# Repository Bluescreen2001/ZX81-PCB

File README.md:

# ZX81-PCB

Recreation of the original ZX81 Issue1 PCB with rounded traces, and the WespiNano, a tiny version of the Wespi.

## DISCLAIMER:

This is for personal use only. You may not sell this design without contacting me.

## Description:

The Sinclair ZX81 was one of the first home computers. There are several PCB versions out there, but the film for the first version was created 
manually with clear foil and stickers and pen. This first version (Issue One) is rare but it is "the original" with non CAD like rounded traces.

One day some people from the German Sinclair [ZX81 forum](https://forum.tlienhard.com) diskussed how this PCB can be recreated.
So I took a photo from front and back side of the PCB with a scanner, put this as a background images in my CAD application and redraw all the traces. 
The resulting DXF file was then imported into EAGLE and than mapped to an EAGLE schematic, so I get a consistent EAGLE project. After some fine tuning 
I got a PCB design which was nearly like the original.

After some diskussions we decided to create a slightly altered version with some "modern" features. See the following chapter ...

## Versions:

### Issue 1:

This is the most authentic version. Nearly like the original with nothing changed at all:

- modulator
- old EPROM
- single resistors instead of SIL arrays

### Issue 1a:

Like Issue 1 above, but a slightly improved silkscreen. Some single resistors are replaced with SIL arrays, but no changes to the PCB traces, 
besides some cosmetic corrections

### Issue 1b:

Some functional addons:

- added connector for a small VideoOut board "under" the modulator footprint. You can omit the modulator and place this connector to add the 
  videoOut board to get an video out connector instead of the RF output. You can also add a WespNano (see below) to get WiFi, Storage and VGA.
- added footprint for a "modern" EPROM with two jumpers to select the page you like.
- added "Fast Wait" logic with a disable jumper
- added a jumper for vLA81 support. This routes the OSC pin of the ULA to A13 of the RAM, so you can use ...
- modern CMOS RAM up to 32 kB, supported by the vLA81

### Issue 1c:

- added an reset button
- added a second mounting hole for the VideoOut board for better stability.

## Addons

### VideoOut

A small addon board fitting onto Issue 1b and higher that features a buffered composite video out cinch connector

### Wespi-Nano

This is a tiny version of the Wespi project from the [ZX81 forum](https://forum.tlienhard.com). It uses an esp32 to scan the video signal to create 
a VGA or TFT video signal. Also it can send files to the ZX's tape input using a fastload mechanism. The files came from the esp's onboard flash memory 
which can be populated using a web interface from your PC or mobile. Loading is initiated by an onscreen menu on the ZX81 screen via load command.

## Hints:
In every subdirectory you find a *_Gerbers.zip. This are the files you need to create the PCB by any PCB manufacturer like JLCPCB.
In the doc directory are some photos and a nice German manual.

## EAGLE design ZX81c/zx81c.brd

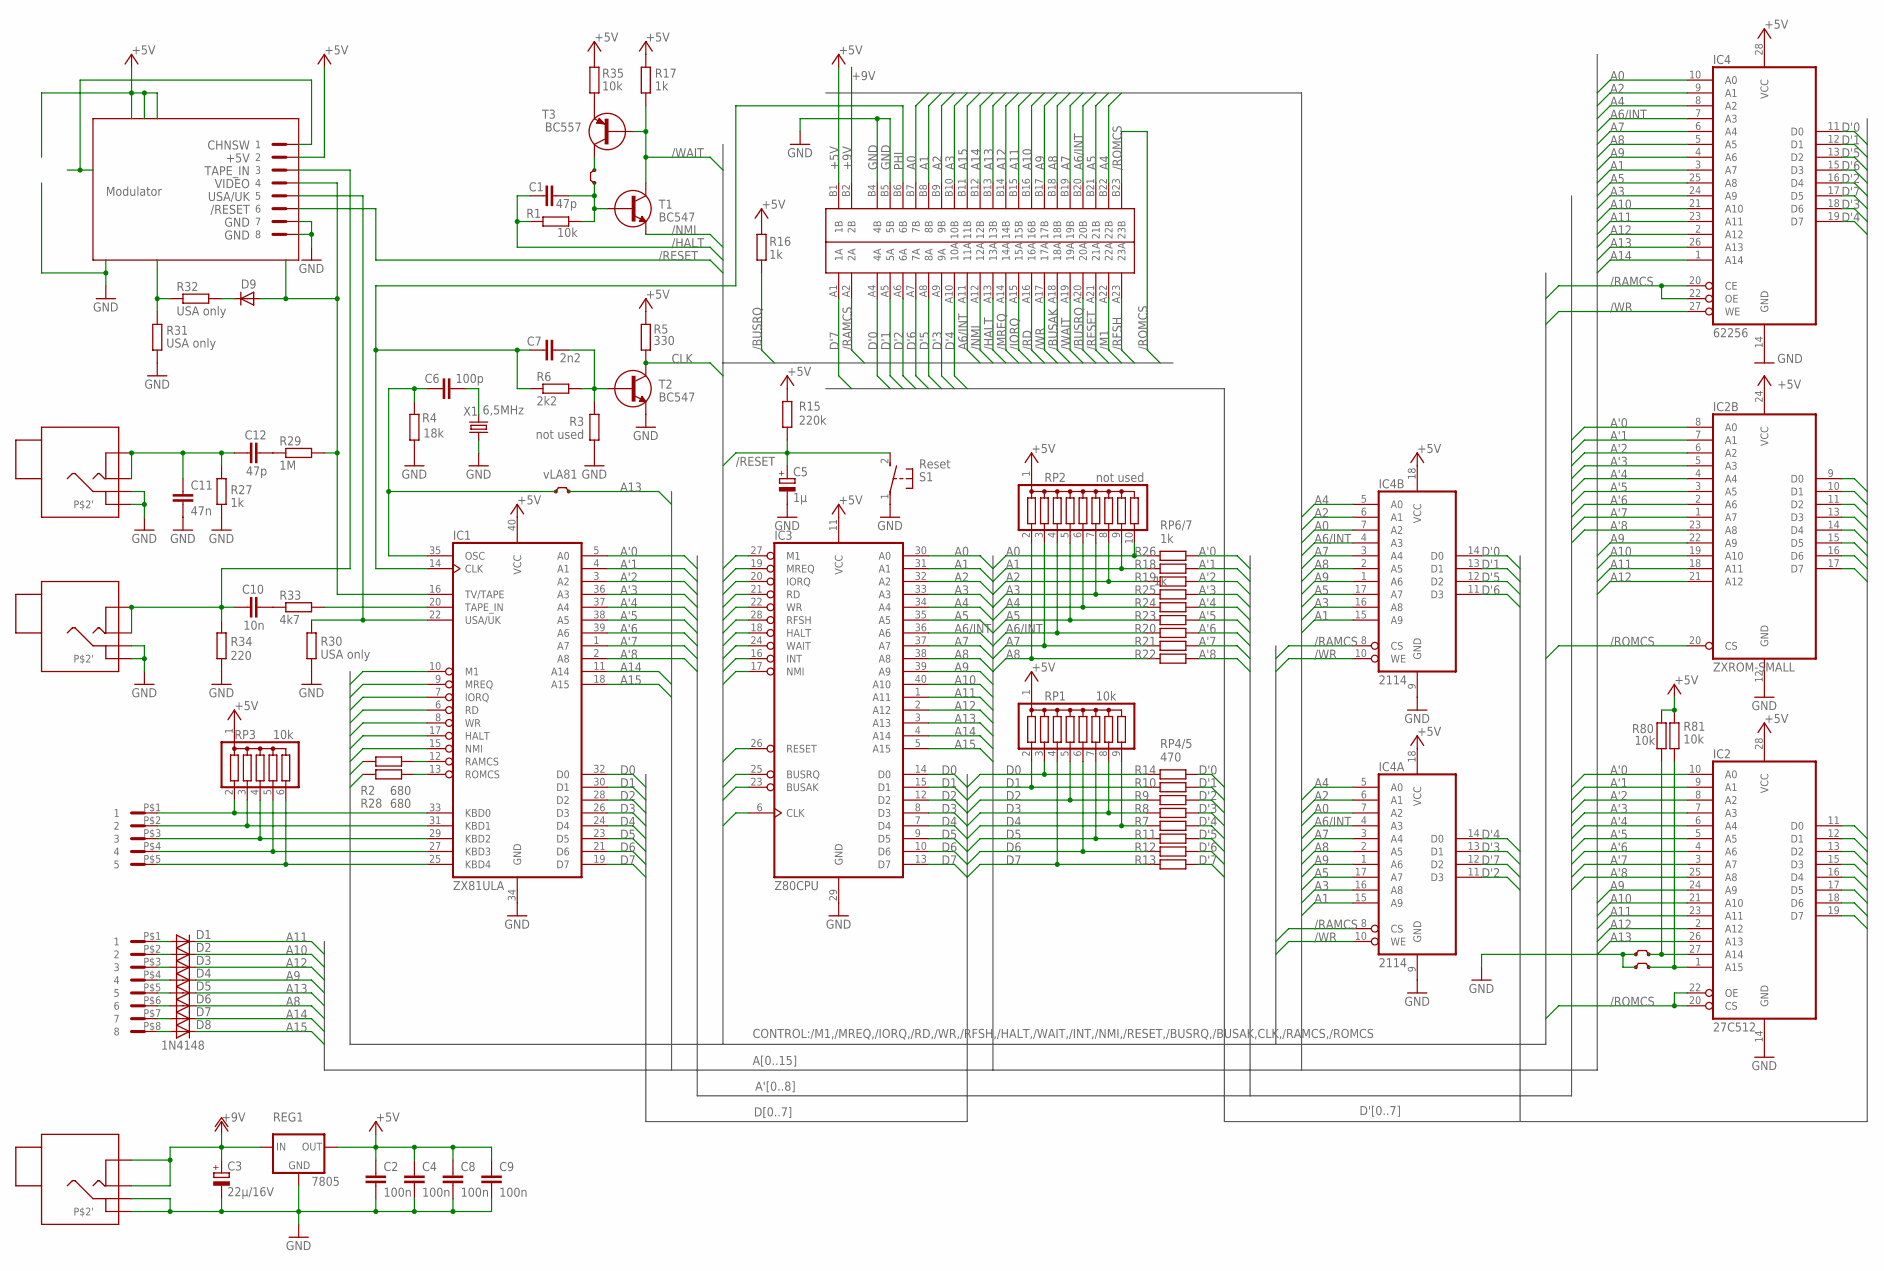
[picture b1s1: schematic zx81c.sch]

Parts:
C1, C12: 47p; C025-025X050
C2, C4, C8, C9: 100n; C025-025X050
C3: 22µ/16V; E5-5
C5: 1µ; E3,8-5
C6: 100p; C025-025X050
C7: 2n2; C025-025X050
C10: 10n; C025-025X050
C11: 47n; C025-025X050
D1, D2, D3, D4, D5, D6, D7, D8: 1N4148; D-TR-10
D9: DIODED15; D15
IC1: ZX81ULA; DIL40
IC2: 27C512; DIL28
IC2B: ZXROM-SMALL; DIL24
IC3: Z80CPU; DIL40
IC4: 62256; DIL28
IC4A, IC4B: 2114; DIL18
JP1, JP2, JP3, JP4: JUMPER
K1: ZX81CONN; ZX81CON
K2: MIC; ZXKLINKE4POL
K3: EAR; ZXKLINKE4POL
K4: DCIN; ZXKLINKE4POL
K5: PINHEAD-2X4; PINHEAD2X4
KB1: ZXKBD5CON; ZXKDB5
KB2: ZXKBD8CON; ZXKBD8
R1, R35, R80, R81: 10k; R207/12
R2, R28: 680; R207/12
R3: not used; R207/12
R4: 18k; R207/12
R5: 330; R207/12
R6: 2k2; R207/12
R15: 220k; R207/12
R16, R17, R27: 1k; R207/12
R29: 1M; R207/12
R30, R31, R32: USA only; R207/12
R33: 4k7; R207/12
R34: 220; R207/12
REG1: 7805; 78XXL
RP1: 10k; SIL9
RP2: not used; SIL10
RP3: 10k; SIL6
RP4, RP5: 470; SIL8P
RP6: 1k; SIL8P
RP7: 1k; SIL10P
S1: Reset; B3F-31XX
T1, T2: BC547; TO92
T3: BC557; TO92
X1: 6,5MHz; HC49

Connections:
+5V: C2.1, C4.1, C8.1, C9.1, IC1.40 (VCC), IC2.28 (VCC), IC2B.24 (VCC), IC3.11 (VCC), IC4.28 (VCC), IC4A.18 (VCC), IC4B.18 (VCC), K1.B1 (1B), K5.2, R5.2, R15.2, R16.1, R17.2, R35.2, R80.2, R81.2, REG1.OUT, RP1.1, RP2.1, RP3.1
+9V: C3.+, K1.B2 (2B), K4.1, K4.1', REG1.IN
/BUSAK: IC3.23 (BUSAK), K1.A18 (18A)
/BUSRQ: IC3.25 (BUSRQ), K1.A20 (20A), R16.2
/HALT: C1.1, IC1.17 (HALT), IC3.18 (HALT), K1.A13 (13A), R1.1
/IORQ: IC1.7 (IORQ), IC3.20 (IORQ), K1.A15 (15A)
/M1: IC1.10 (M1), IC3.27 (M1), K1.A22 (22A)
/MREQ: IC1.9 (MREQ), IC3.19 (MREQ), K1.A14 (14A)
/NMI: IC1.15 (NMI), IC3.17 (NMI), K1.A12 (12A), T1.E
/RAMCS: IC4.20 (CE), IC4.22 (OE), IC4A.8 (CS), IC4B.8 (CS), K1.A2 (2A), R2.2
/RD: IC1.6 (RD), IC3.21 (RD), K1.A16 (16A)
/RESET: C5.+, IC3.26 (RESET), K1.A21 (21A), K5.6, R15.1, S1.2 (S)
/RFSH: IC3.28 (RFSH), K1.A23 (23A)
/ROMCS: IC2.20 (CS), IC2.22 (OE), IC2B.20 (CS), K1.B23 (23B), R28.2
/WAIT: IC3.24 (WAIT), K1.A19 (19A), R17.1, T1.C, T3.B
/WR: IC1.8 (WR), IC3.22 (WR), IC4.27 (WE), IC4A.10 (WE), IC4B.10 (WE), K1.A17 (17A)
A0: IC3.30 (A0), IC4.10 (A0), IC4A.7 (A2), IC4B.7 (A2), K1.B7 (7B), RP2.10, RP6.8 (2)
A1: IC3.31 (A1), IC4.3 (A7), IC4A.15 (A9), IC4B.15 (A9), K1.B8 (8B), RP2.9, RP7.1
A2: IC3.32 (A2), IC4.9 (A1), IC4A.6 (A1), IC4B.6 (A1), K1.B9 (9B), RP2.8, RP7.4 (2)
A3: IC3.33 (A3), IC4.24 (A9), IC4A.16 (A8), IC4B.16 (A8), K1.B10 (10B), RP2.7, RP6.6 (2)
A4: IC3.34 (A4), IC4.8 (A2), IC4A.5 (A0), IC4B.5 (A0), K1.B22 (22B), RP2.6, RP6.4 (2)
A5: IC3.35 (A5), IC4.25 (A8), IC4A.17 (A7), IC4B.17 (A7), K1.B21 (21B), RP2.5, RP6.2
A6/INT: IC3.16 (INT), IC3.36 (A6), IC4.7 (A3), IC4A.4 (A3), IC4B.4 (A3), K1.A11 (11A), K1.B20 (20B), RP2.4, RP7.6 (2)
A7: IC3.37 (A7), IC4.6 (A4), IC4A.3 (A4), IC4B.3 (A4), K1.B19 (19B), RP2.3, RP7.8 (2)
A8: D6.C, IC3.38 (A8), IC4.5 (A5), IC4A.2 (A5), IC4B.2 (A5), K1.B18 (18B), RP2.2, RP7.10 (2)
A9: D4.C, IC2.24 (A9), IC2B.22 (A9), IC3.39 (A9), IC4.4 (A6), IC4A.1 (A6), IC4B.1 (A6), K1.B17 (17B)
A10: D2.C, IC2.21 (A10), IC2B.19 (A10), IC3.40 (A10), IC4.21 (A10), K1.B16 (16B)
A11: D1.C, IC2.23 (A11), IC2B.18 (A11), IC3.1 (A11), IC4.23 (A11), K1.B15 (15B)
A12: D3.C, IC2.2 (A12), IC2B.21 (A12), IC3.2 (A12), IC4.2 (A12), K1.B14 (14B)
A13: D5.C, IC2.26 (A13), IC3.3 (A13), IC4.26 (A13), JP3.2, K1.B13 (13B)
A14: D7.C, IC1.11 (A14), IC3.4 (A14), IC4.1 (A14), K1.B12 (12B)
A15: D8.C, IC1.18 (A15), IC3.5 (A15), K1.B11 (11B)
A'0: IC1.5 (A0), IC2.10 (A0), IC2B.8 (A0), RP6.7 (1)
A'1: IC1.4 (A1), IC2.9 (A1), IC2B.7 (A1), RP7.2
A'2: IC1.3 (A2), IC2.8 (A2), IC2B.6 (A2), RP7.3 (1)
A'3: IC1.36 (A3), IC2.7 (A3), IC2B.5 (A3), RP6.5 (1)
A'4: IC1.37 (A4), IC2.6 (A4), IC2B.4 (A4), RP6.3 (1)
A'5: IC1.38 (A5), IC2.5 (A5), IC2B.3 (A5), RP6.1
A'6: IC1.39 (A6), IC2.4 (A6), IC2B.2 (A6), RP7.5 (1)
A'7: IC1.1 (A7), IC2.3 (A7), IC2B.1 (A7), RP7.7 (1)
A'8: IC1.2 (A8), IC2.25 (A8), IC2B.23 (A8), RP7.9 (1)
CHNSW: K5.1
CLK: IC3.6 (CLK), R5.1, T2.C
D0: IC1.32 (D0), IC3.14 (D0), RP1.3, RP5.7 (1)
D1: IC1.30 (D1), IC3.15 (D1), RP1.2, RP4.7 (1)
D2: IC1.28 (D2), IC3.12 (D2), RP1.5, RP4.5 (1)
D3: IC1.26 (D3), IC3.8 (D3), RP1.8, RP4.3 (1)
D4: IC1.24 (D4), IC3.7 (D4), RP1.9, RP4.2
D5: IC1.23 (D5), IC3.9 (D5), RP1.7, RP5.2
D6: IC1.21 (D6), IC3.10 (D6), RP1.6, RP5.3 (1)
D7: IC1.19 (D7), IC3.13 (D7), RP1.4, RP5.6 (2)
D'0: IC2.11 (D0), IC2B.9 (D0), IC4.11 (D0), IC4B.14 (D0), K1.A4 (4A), RP5.8 (2)
D'1: IC2.12 (D1), IC2B.10 (D1), IC4.12 (D1), IC4B.13 (D1), K1.A5 (5A), RP4.8 (2)
D'2: IC2.13 (D2), IC2B.11 (D2), IC4.16 (D4), IC4A.11 (D3), K1.A6 (6A), RP4.6 (2)
D'3: IC2.15 (D3), IC2B.13 (D3), IC4.18 (D6), IC4A.13 (D1), K1.A9 (9A), RP4.4 (2)
D'4: IC2.16 (D4), IC2B.14 (D4), IC4.19 (D7), IC4A.14 (D0), K1.A10 (10A), RP4.1
D'5: IC2.17 (D5), IC2B.15 (D5), IC4.13 (D2), IC4B.12 (D2), K1.A8 (8A), RP5.1
D'6: IC2.18 (D6), IC2B.16 (D6), IC4.15 (D3), IC4B.11 (D3), K1.A7 (7A), RP5.4 (2)
D'7: IC2.19 (D7), IC2B.17 (D7), IC4.17 (D5), IC4A.12 (D2), K1.A1 (1A), RP5.5 (1)
GND: C2.2, C3.-, C4.2, C5.-, C8.2, C9.2, C11.2, IC1.34 (GND), IC2.14 (GND), IC2B.12 (GND), IC3.29 (GND), IC4.14 (GND), IC4A.9 (GND), IC4B.9 (GND), JP1.1, JP2.1, K1.B4 (4B), K1.B5 (5B), K2.2, K2.2', K3.2, K3.2', K4.2, K4.2', K5.7, K5.8, R3.1, R4.1, R27.1, R30.2, R31.1, R34.1, REG1.GND, S1.1, T2.E, X1.1
KBD0: IC1.33 (KBD0), KB1.P$1 (1), RP3.2
KBD1: IC1.31 (KBD1), KB1.P$2 (2), RP3.3
KBD2: IC1.29 (KBD2), KB1.P$3 (3), RP3.4
KBD3: IC1.27 (KBD3), KB1.P$4 (4), RP3.5
KBD4: IC1.25 (KBD4), KB1.P$5 (5), RP3.6
unnamed: IC1.12 (RAMCS), R2.1
unnamed: IC1.13 (ROMCS), R28.1
unnamed: C1.2, JP4.1, R1.2, T1.B
unnamed: C6.2, X1.2
unnamed: C6.1, IC1.35 (OSC), JP3.1, R4.2
unnamed: C7.2, R3.2, R6.2, T2.B
unnamed: IC2.27 (A14), JP1.2, R80.1
unnamed: D1.A, KB2.P$1 (1)
unnamed: D2.A, KB2.P$2 (2)
unnamed: D3.A, KB2.P$3 (3)
unnamed: D4.A, KB2.P$4 (4)
unnamed: D5.A, KB2.P$5 (5)
unnamed: D6.A, KB2.P$6 (6)
unnamed: D7.A, KB2.P$7 (7)
unnamed: D8.A, KB2.P$8 (8)
unnamed: C10.2, R33.1
unnamed: C12.2, R29.1
unnamed: IC2.1 (A15), JP2.2, R81.1
unnamed: D9.C, R32.2
unnamed: R35.1, T3.E
unnamed: R31.2, R32.1
unnamed: JP4.2, T3.C
PHI: C7.1, IC1.14 (CLK), K1.B6 (6B), R6.1
TAPEIN: IC1.20 (TAPE_IN), R33.2
TAPE_IN: C10.1, K3.1, K3.1', K5.3, R34.2
TAPE_OUT: C11.1, C12.1, K2.1, K2.1', R27.2
USA/UK: IC1.22 (USA/UK), K5.5, R30.1
VIDEO: D9.A, IC1.16 (TV/TAPE), K5.4, R29.2

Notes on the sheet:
R10
R12
R13
R11
R14
RP4/5 470
R26
R18
R19
R25
R24
R23
R20
R21
R22
RP6/7 1k
Modulator
vLA81

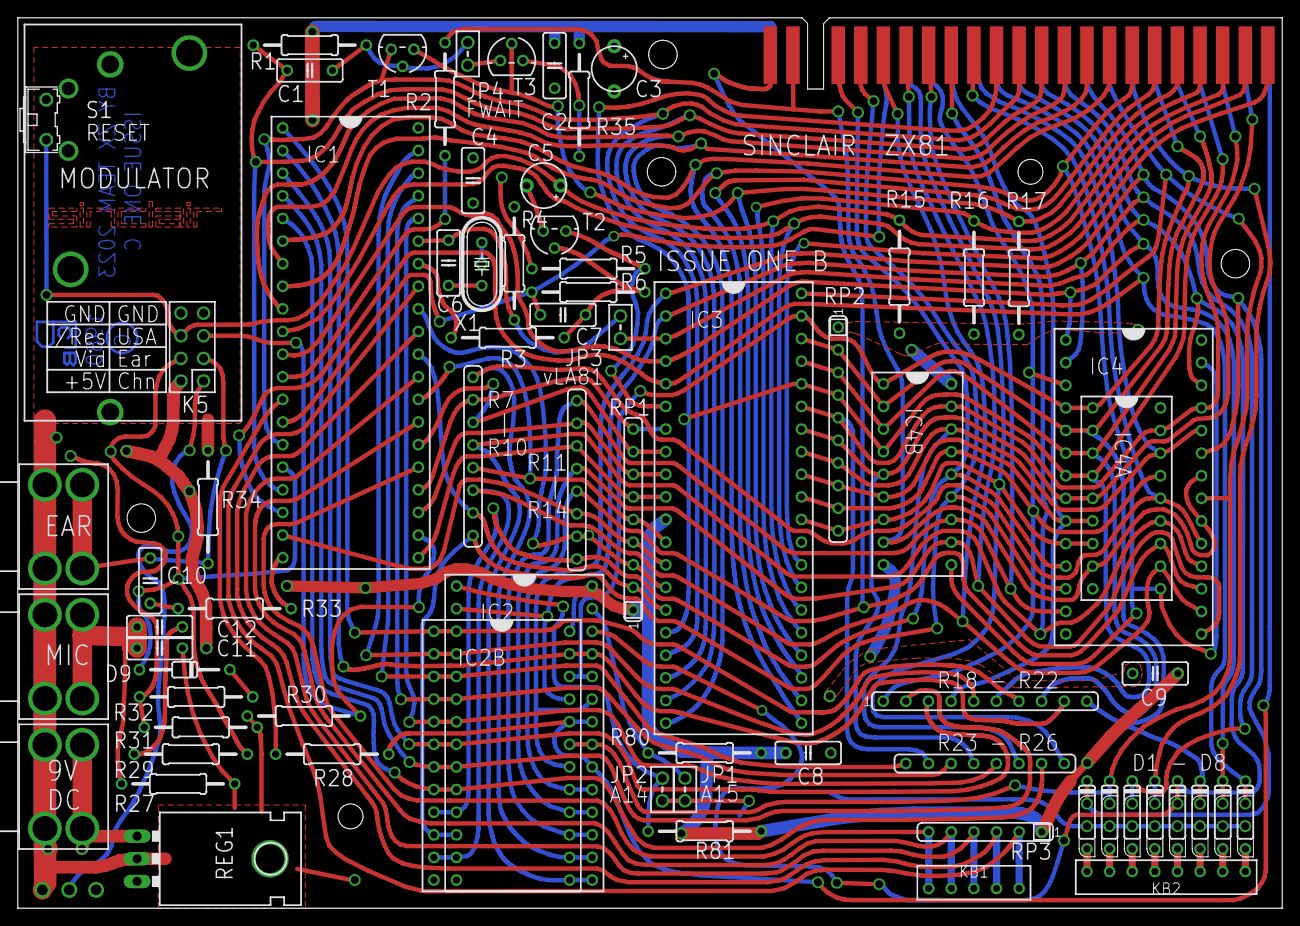
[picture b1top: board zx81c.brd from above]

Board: 2 copper layers, 142.0 x 100.0 mm, 72 parts (0 on the bottom side), 92 nets.

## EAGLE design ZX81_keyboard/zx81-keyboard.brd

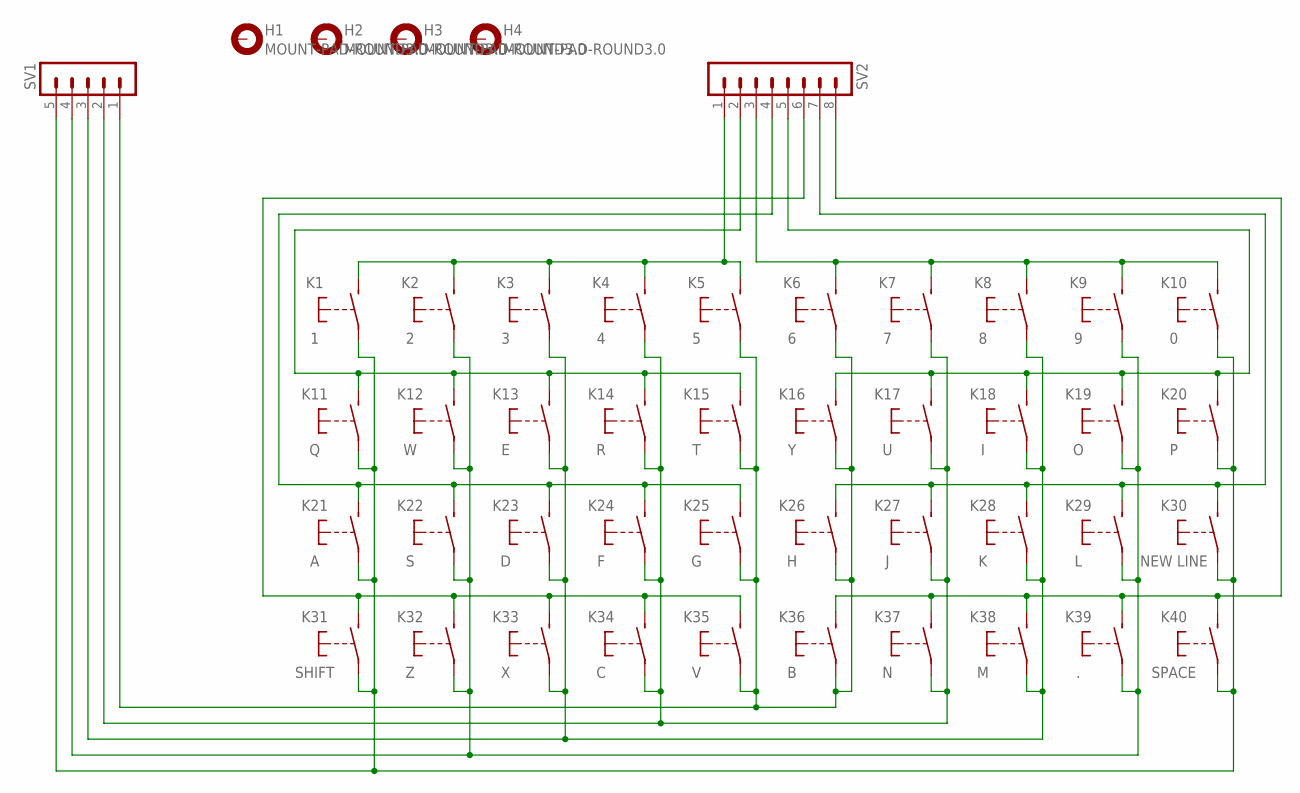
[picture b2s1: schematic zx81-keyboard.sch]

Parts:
H1, H2, H3, H4: MOUNT-PAD-ROUND3.0; 3,0-PAD
K1: 1; MARQUARTDT-6425
K2: 2; MARQUARTDT-6425
K3: 3; MARQUARTDT-6425
K4: 4; MARQUARTDT-6425
K5: 5; MARQUARTDT-6425
K6: 6; MARQUARTDT-6425
K7: 7; MARQUARTDT-6425
K8: 8; MARQUARTDT-6425
K9: 9; MARQUARTDT-6425
K10: 0; MARQUARTDT-6425
K11: Q; MARQUARTDT-6425
K12: W; MARQUARTDT-6425
K13: E; MARQUARTDT-6425
K14: R; MARQUARTDT-6425
K15: T; MARQUARTDT-6425
K16: Y; MARQUARTDT-6425
K17: U; MARQUARTDT-6425
K18: I; MARQUARTDT-6425
K19: O; MARQUARTDT-6425
K20: P; MARQUARTDT-6425
K21: A; MARQUARTDT-6425
K22: S; MARQUARTDT-6425
K23: D; MARQUARTDT-6425
K24: F; MARQUARTDT-6425
K25: G; MARQUARTDT-6425
K26: H; MARQUARTDT-6425
K27: J; MARQUARTDT-6425
K28: K; MARQUARTDT-6425
K29: L; MARQUARTDT-6425
K30: NEW LINE; MARQUARTDT-6425
K31: SHIFT; MARQUARTDT-6425
K32: Z; MARQUARTDT-6425
K33: X; MARQUARTDT-6425
K34: C; MARQUARTDT-6425
K35: V; MARQUARTDT-6425
K36: B; MARQUARTDT-6425
K37: N; MARQUARTDT-6425
K38: M; MARQUARTDT-6425
K39: .; MARQUARTDT-6425
K40: SPACE; MARQUARTDT-6425
SV1: MA05-1
SV2: MA08-1

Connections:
unnamed: K1.P$2 (S), K2.P$2 (S), K3.P$2 (S), K4.P$2 (S), K5.P$2 (S), SV2.1
unnamed: K6.P$2 (S), K7.P$2 (S), K8.P$2 (S), K9.P$2 (S), K10.P$2 (S), SV2.3
unnamed: K11.P$2 (S), K12.P$2 (S), K13.P$2 (S), K14.P$2 (S), K15.P$2 (S), SV2.2
unnamed: K21.P$2 (S), K22.P$2 (S), K23.P$2 (S), K24.P$2 (S), K25.P$2 (S), SV2.4
unnamed: K31.P$2 (S), K32.P$2 (S), K33.P$2 (S), K34.P$2 (S), K35.P$2 (S), SV2.6
unnamed: K16.P$2 (S), K17.P$2 (S), K18.P$2 (S), K19.P$2 (S), K20.P$2 (S), SV2.5
unnamed: K26.P$2 (S), K27.P$2 (S), K28.P$2 (S), K29.P$2 (S), K30.P$2 (S), SV2.7
unnamed: K36.P$2 (S), K37.P$2 (S), K38.P$2 (S), K39.P$2 (S), K40.P$2 (S), SV2.8
unnamed: K5.P$1, K6.P$1, K15.P$1, K16.P$1, K25.P$1, K26.P$1, K35.P$1, K36.P$1, SV1.1
unnamed: K4.P$1, K7.P$1, K14.P$1, K17.P$1, K24.P$1, K27.P$1, K34.P$1, K37.P$1, SV1.2
unnamed: K3.P$1, K8.P$1, K13.P$1, K18.P$1, K23.P$1, K28.P$1, K33.P$1, K38.P$1, SV1.3
unnamed: K2.P$1, K9.P$1, K12.P$1, K19.P$1, K22.P$1, K29.P$1, K32.P$1, K39.P$1, SV1.4
unnamed: K1.P$1, K10.P$1, K11.P$1, K20.P$1, K21.P$1, K30.P$1, K31.P$1, K40.P$1, SV1.5

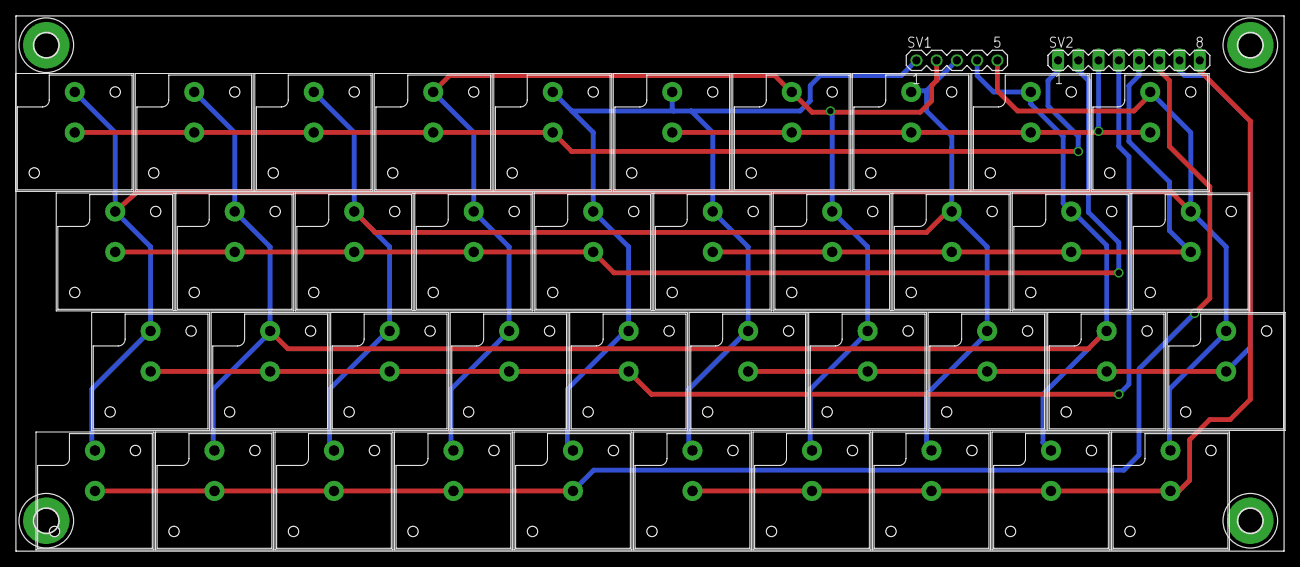
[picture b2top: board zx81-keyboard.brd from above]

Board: 2 copper layers, 159.2 x 67.2 mm, 46 parts (0 on the bottom side), 13 nets.

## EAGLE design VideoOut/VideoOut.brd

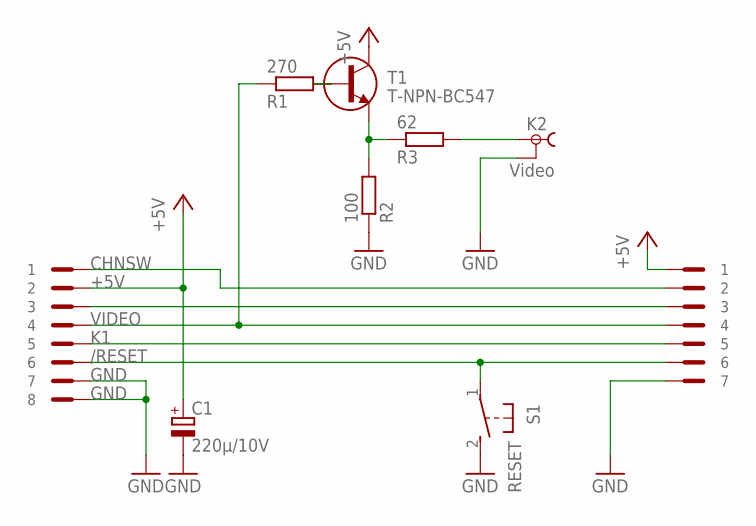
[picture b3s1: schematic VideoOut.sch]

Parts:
C1: 220µ/10V; E2,5-6
K2: Video; TOBU3
K3: PINHEAD-1X7; PINHEAD1X7
K6: PINHEAD-2X4; PINHEAD2X4
R1: 270; R207/10
R2: 100; R207/10
R3: 62; R207/10
S1: RESET; B3F-31XX
T1: T-NPN-BC547; TO92

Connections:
+5V: C1.+, K3.1, K6.2, T1.C
/RESET: K3.6, K6.6, S1.1
CHNSW: K3.2, K6.1
GND: C1.-, K2.2, K2.2@1 (2), K2.2@2 (2), K3.7, K6.7, K6.8, R2.1, S1.2 (S)
K1: K3.5, K6.5
unnamed: K3.3, K6.3
unnamed: R1.2, T1.B
unnamed: R2.2, R3.1, T1.E
unnamed: K2.1, R3.2
VIDEO: K3.4, K6.4, R1.1

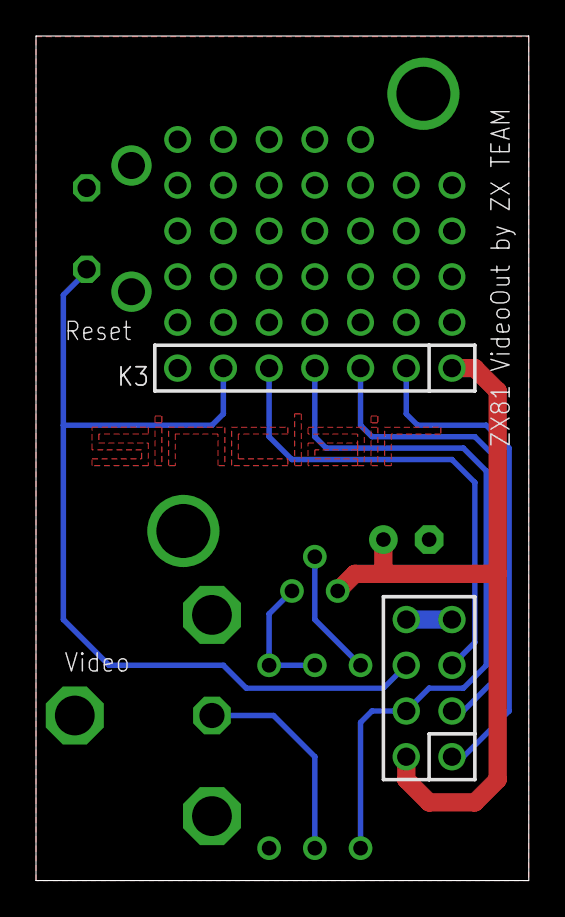
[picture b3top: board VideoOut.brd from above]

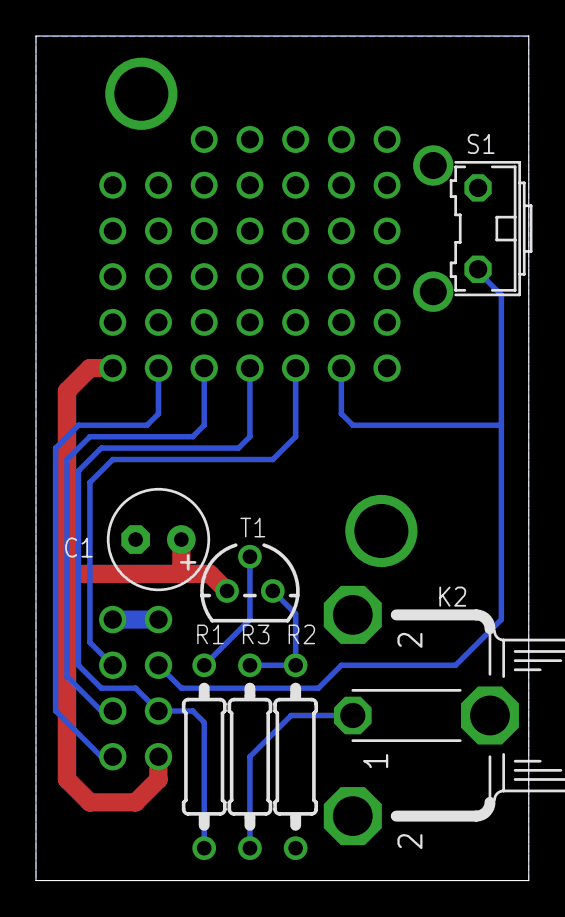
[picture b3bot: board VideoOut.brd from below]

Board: 2 copper layers, 27.4 x 46.9 mm, 9 parts (7 on the bottom side), 10 nets.

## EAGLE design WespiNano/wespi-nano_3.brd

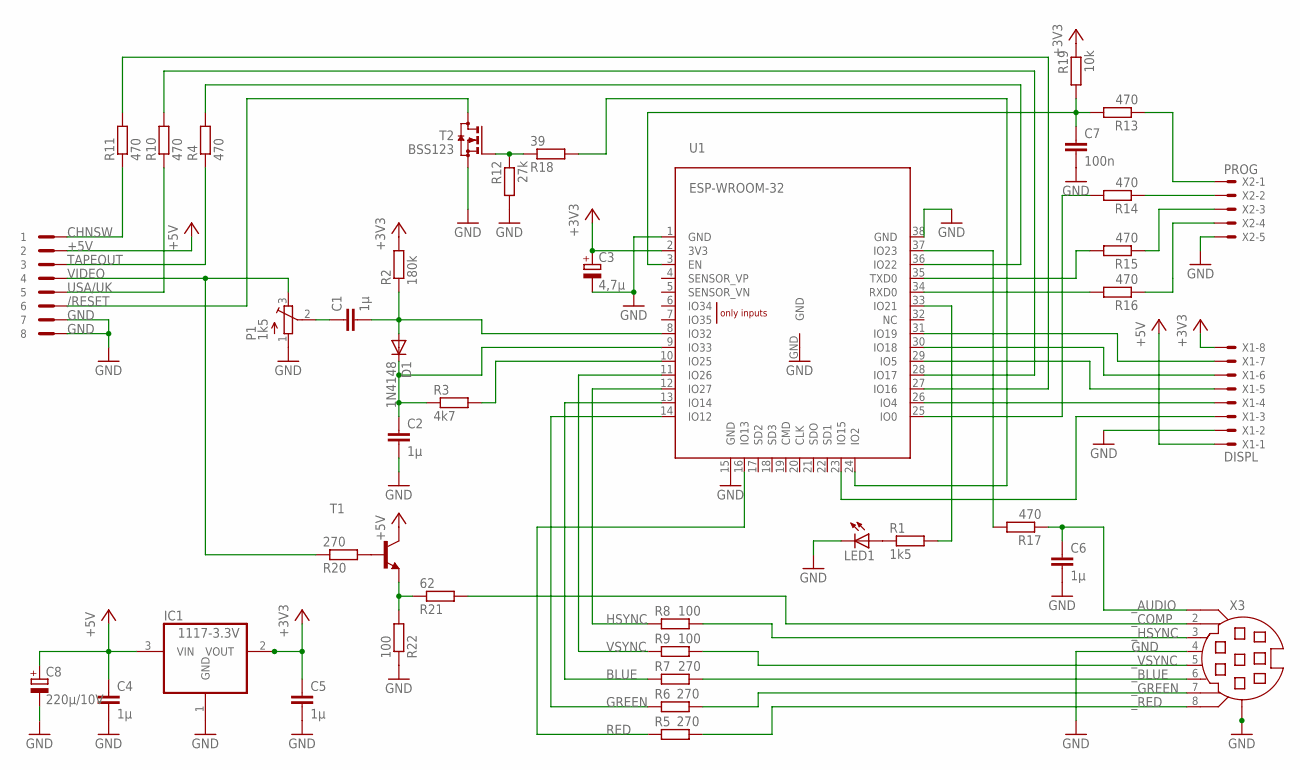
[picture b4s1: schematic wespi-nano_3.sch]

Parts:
C1, C2, C4, C5, C6: 1µ; C0805
C3: 4,7µ; 153CLV-0405
C7: 100n; C0805
C8: 220µ/10V; E2,5-6
D1: 1N4148; SOD-123_MINI-SMA
IC1: 1117-3.3V; SOT223
K6: PINHEAD-2X4; PINHEAD2X4
LED1: LEDSML0805; SML0805
P1: 1k5; 3223G
R1: 1k5; R0805
R2: 180k; R0805
R3: 4k7; R0805
R4, R10, R11, R13, R14, R15, R16, R17: 470; R0805
R5, R6, R7, R20: 270; R0805
R8, R9, R22: 100; R0805
R12: 27k; R0805
R18: 39; R0805
R19: 10k; R0805
R21: 62; R0805
T1: BC847-NPN-SOT23-BEC; SOT23-BEC
T2: BSS123; SOT23
U1: ESP-WROOM-32
X1: DISPL; 53047-08
X2: PROG; 53047-05
X3: MINI-DIN-8

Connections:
+3V3: C3.+, C5.1, IC1.2 (VOUT), IC1.4 (VOUT1), R2.2, R19.1, U1.2 (3V3), X1.8
+5V: C4.1, C8.+, IC1.3 (VIN), K6.2, T1.C, X1.1
/RESET: K6.6, T2.3 (D)
BLUE: R7.1, U1.13 (IO14)
BOOT0: R14.1, X2.2
CHNSW: K6.1, R11.1
GND: C2.2, C3.-, C4.2, C5.2, C6.2, C7.2, C8.-, IC1.1 (GND), K6.7, K6.8, LED1.C, P1.1 (A), R12.2, R22.1, T2.2 (S), U1.1 (GND), U1.15 (GND), U1.38 (GND), U1.GND, X1.2, X2.5, X3.4, X3.G (G1), X3.G1 (G2), X3.G2 (G3)
GREEN: R6.1, U1.14 (IO12)
HSYNC: R8.1, U1.12 (IO27)
IO0: R14.2, U1.25 (IO0)
unnamed: K6.3, R4.1
unnamed: U1.23 (IO15), X1.3
unnamed: C1.2, D1.A, R2.1, U1.8 (IO32)
unnamed: C2.1, D1.C, R3.1, U1.9 (IO33)
unnamed: R3.2, U1.10 (IO25)
unnamed: R20.2, T1.B
unnamed: R21.1, R22.2, T1.E
unnamed: LED1.A, R1.1
unnamed: C1.1, P1.2 (S)
unnamed: R1.2, U1.33 (IO21)
unnamed: R18.2, U1.24 (IO2)
unnamed: U1.26 (IO4), X1.4
unnamed: R10.2, U1.28 (IO17)
unnamed: R11.2, U1.27 (IO16)
unnamed: U1.29 (IO5), X1.5
unnamed: U1.30 (IO18), X1.6
unnamed: U1.31 (IO19), X1.7
unnamed: R12.1, R18.1, T2.1 (G)
unnamed: R17.2, U1.37 (IO23)
RED: R5.1, U1.16 (IO13)
RESET: C7.1, R13.2, R19.2, U1.3 (EN)
RXD0: R16.2, U1.34 (RXD0)
TAPEOUT: R4.2, U1.36 (IO22)
TXD0: R15.2, U1.35 (TXD0)
USA/UK: K6.5, R10.1
VIDEO: K6.4, P1.3 (E), R20.1
VSYNC: R9.1, U1.11 (IO26)
_AUDIO: C6.1, R17.1, X3.1
_BLUE: R7.2, X3.6
_COMP: R21.2, X3.2
_GREEN: R6.2, X3.7
_HSYNC: R8.2, X3.3
_RED: R5.2, X3.8
_RESET: R13.1, X2.1
_RXD: R16.1, X2.4
_TXD: R15.1, X2.3
_VSYNC: R9.2, X3.5

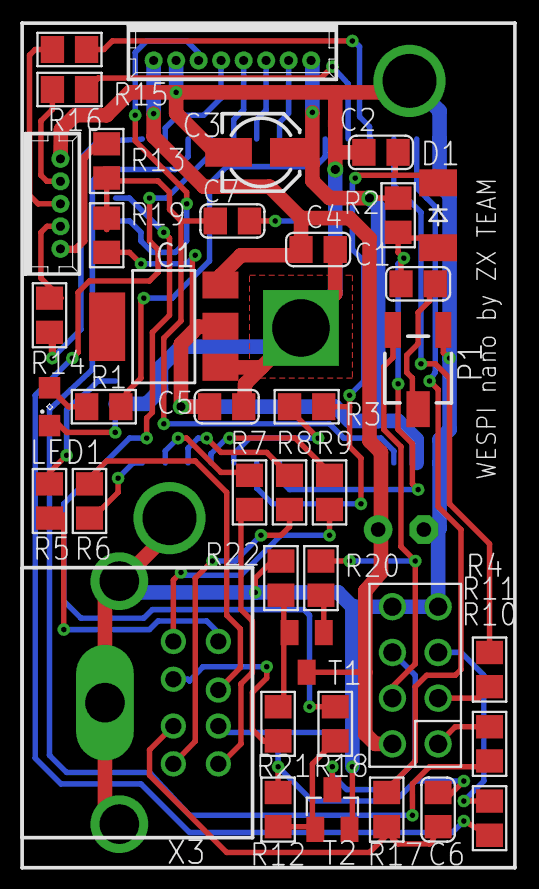
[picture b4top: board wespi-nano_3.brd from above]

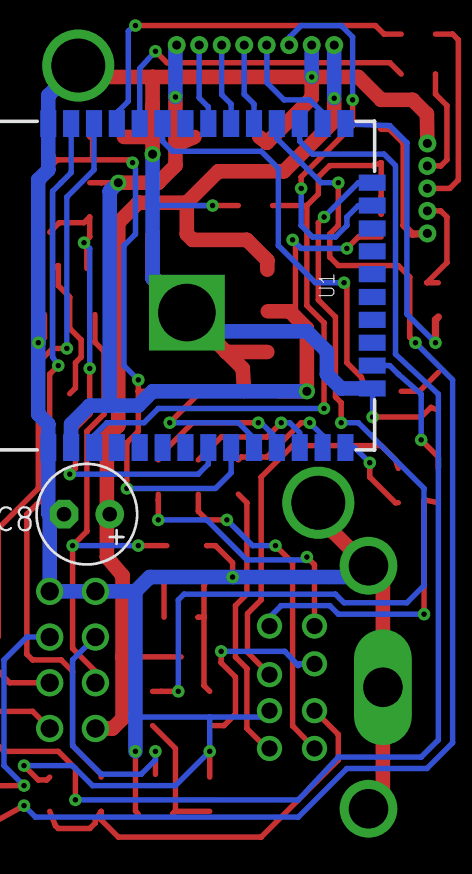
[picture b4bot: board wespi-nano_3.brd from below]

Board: 2 copper layers, 41 parts (2 on the bottom side), 47 nets.

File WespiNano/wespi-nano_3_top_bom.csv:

Comment,Designator,Footprint,LCSC Part #
,LED1,SML0805,
,T1,SOT23-BEC,
1N4148,D1,SOD-123_MINI-SMA,
1k5,P1,3223G,
1µ,C1 C2 C4 C5 C6,C0805,
4 7µ,C3,153CLV-0405,
4k7,R3,R0805,
10k,R19,R0805,
27k,R12,R0805,
39,R18,R0805,
62,R21,R0805,
100,R8 R9 R22,R0805,
100n,C7,C0805,
180k,R1 R2,R0805,
270,R5 R6 R7 R20,R0805,
470,R4 R10 R11 R13 R14 R15 R16 R17,R0805,
1117-3.3V,IC1,SOT223,
BSS123,T2,SOT23,

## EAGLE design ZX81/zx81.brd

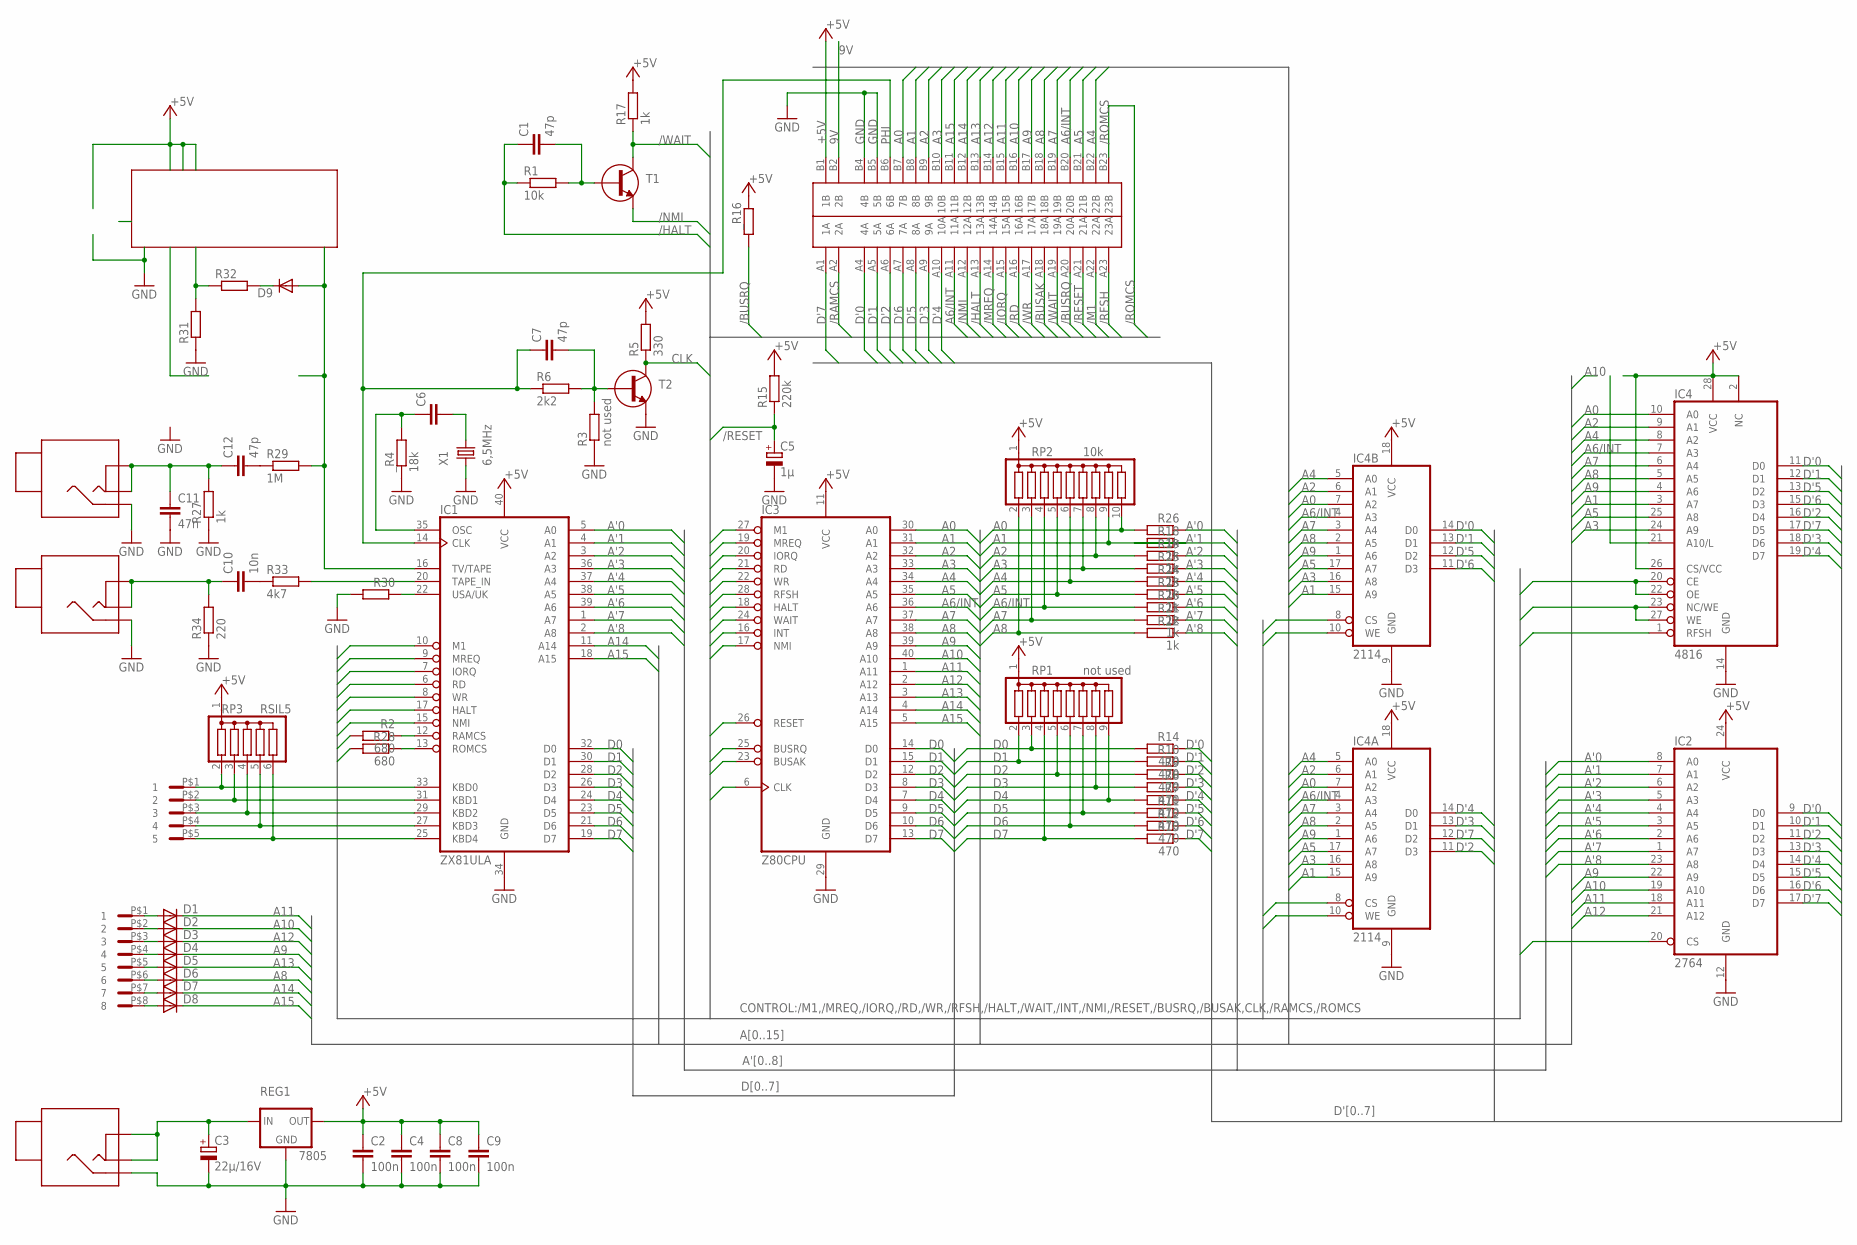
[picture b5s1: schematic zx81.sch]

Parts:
C1, C7, C12: 47p; C025-025X050
C2, C4, C8, C9: 100n; C025-025X050
C3: 22µ/16V; E5-5
C5: 1µ; E3,8-5
C6: C; C025-025X050
C10: 10n; C025-025X050
C11: 47n; C025-025X050
D1, D2, D3, D4, D5, D6, D7, D8: DIODED10; D10
D9: DIODED15; D15
IC1: ZX81ULA; DIL40
IC2: 2764; DIL24
IC3: Z80CPU; DIL40
IC4: 4816; DIL28
IC4A, IC4B: 2114; DIL18
K1: ZX81CONN; ZX81CON
K2: MIC; ZXKLINKE
K3: EAR; ZXKLINKE
K4: DCIN; ZXKLINKE
KB1: ZXKBD5CON; ZXKDB5
KB2: ZXKBD8CON; ZXKBD8
R1: 10k; R207/12
R2, R28: 680; R207/12
R3: not used; R207/12
R5: 330; R207/12
R6: 2k2; R207/12
R7, R8, R9, R10, R11, R12, R13, R14: 470; RV
R15: 220k; R207/12
R17, R27: 1k; R207/12
R18, R19, R20, R21, R22, R23, R24, R25, R26: 1k; RV
R29: 1M; R207/12
R30, R31, R32: RR207/12; R207/12
R33: 4k7; R207/12
R34: 220; R207/12
REG1: 7805; 78XXL
RP1: not used; SIL9
RP2: 10k; SIL10
RP3: RSIL5; SIL6
T1, T2: T-NPN-ZTX313TO92FLAT; TO92FLAT
X1: 6,5MHz; HC49
_R4: 18k; R207/12
_R16: RR207/12; R207/12

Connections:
9V: K1.B2 (2B)
+5V: C2.1, C4.1, C8.1, C9.1, IC1.40 (VCC), IC2.24 (VCC), IC3.11 (VCC), IC4.2 (NC), IC4.26 (CS/VCC), IC4.28 (VCC), IC4A.18 (VCC), IC4B.18 (VCC), K1.B1 (1B), R5.2, R15.2, R17.2, REG1.OUT, RP1.1, RP2.1, RP3.1, _R16.1
/BUSAK: IC3.23 (BUSAK), K1.A18 (18A)
/BUSRQ: IC3.25 (BUSRQ), K1.A20 (20A), _R16.2
/HALT: C1.1, IC1.17 (HALT), IC3.18 (HALT), K1.A13 (13A), R1.1
/IORQ: IC1.7 (IORQ), IC3.20 (IORQ), K1.A15 (15A)
/M1: IC1.10 (M1), IC3.27 (M1), K1.A22 (22A)
/MREQ: IC1.9 (MREQ), IC3.19 (MREQ), K1.A14 (14A)
/NMI: IC1.15 (NMI), IC3.17 (NMI), K1.A12 (12A), T1.3 (E)
/RAMCS: IC4.20 (CE), IC4.22 (OE), IC4A.8 (CS), IC4B.8 (CS), K1.A2 (2A), R2.2
/RD: IC1.6 (RD), IC3.21 (RD), K1.A16 (16A)
/RESET: C5.+, IC3.26 (RESET), K1.A21 (21A), R15.1
/RFSH: IC3.28 (RFSH), IC4.1 (RFSH), K1.A23 (23A)
/ROMCS: IC2.20 (CS), K1.B23 (23B), R28.2
/WAIT: IC3.24 (WAIT), K1.A19 (19A), R17.1, T1.2 (C)
/WR: IC1.8 (WR), IC3.22 (WR), IC4.23 (NC/WE), IC4.27 (WE), IC4A.10 (WE), IC4B.10 (WE), K1.A17 (17A)
A0: IC3.30 (A0), IC4.10 (A0), IC4A.7 (A2), IC4B.7 (A2), K1.B7 (7B), R26.2, RP2.10
A1: IC3.31 (A1), IC4.3 (A7), IC4A.15 (A9), IC4B.15 (A9), K1.B8 (8B), R18.1, RP2.9
A2: IC3.32 (A2), IC4.9 (A1), IC4A.6 (A1), IC4B.6 (A1), K1.B9 (9B), R19.2, RP2.8
A3: IC3.33 (A3), IC4.24 (A9), IC4A.16 (A8), IC4B.16 (A8), K1.B10 (10B), R25.2, RP2.7
A4: IC3.34 (A4), IC4.8 (A2), IC4A.5 (A0), IC4B.5 (A0), K1.B22 (22B), R24.2, RP2.6
A5: IC3.35 (A5), IC4.25 (A8), IC4A.17 (A7), IC4B.17 (A7), K1.B21 (21B), R23.2, RP2.5
A6/INT: IC3.16 (INT), IC3.36 (A6), IC4.7 (A3), IC4A.4 (A3), IC4B.4 (A3), K1.A11 (11A), K1.B20 (20B), R20.2, RP2.4
A7: IC3.37 (A7), IC4.6 (A4), IC4A.3 (A4), IC4B.3 (A4), K1.B19 (19B), R21.2, RP2.3
A8: D6.C, IC3.38 (A8), IC4.5 (A5), IC4A.2 (A5), IC4B.2 (A5), K1.B18 (18B), R22.2, RP2.2
A9: D4.C, IC2.22 (A9), IC3.39 (A9), IC4.4 (A6), IC4A.1 (A6), IC4B.1 (A6), K1.B17 (17B)
A10: D2.C, IC2.19 (A10), IC3.40 (A10), K1.B16 (16B)
A10/L: IC4.21 (A10/L)
A11: D1.C, IC2.18 (A11), IC3.1 (A11), K1.B15 (15B)
A12: D3.C, IC2.21 (A12), IC3.2 (A12), K1.B14 (14B)
A13: D5.C, IC3.3 (A13), K1.B13 (13B)
A14: D7.C, IC1.11 (A14), IC3.4 (A14), K1.B12 (12B)
A15: D8.C, IC1.18 (A15), IC3.5 (A15), K1.B11 (11B)
A'0: IC1.5 (A0), IC2.8 (A0), R26.1
A'1: IC1.4 (A1), IC2.7 (A1), R18.2
A'2: IC1.3 (A2), IC2.6 (A2), R19.1
A'3: IC1.36 (A3), IC2.5 (A3), R25.1
A'4: IC1.37 (A4), IC2.4 (A4), R24.1
A'5: IC1.38 (A5), IC2.3 (A5), R23.1
A'6: IC1.39 (A6), IC2.2 (A6), R20.1
A'7: IC1.1 (A7), IC2.1 (A7), R21.1
A'8: IC1.2 (A8), IC2.23 (A8), R22.1
CLK: IC3.6 (CLK), R5.1, T2.2 (C)
D0: IC1.32 (D0), IC3.14 (D0), R14.2, RP1.3
D1: IC1.30 (D1), IC3.15 (D1), R10.2, RP1.2
D2: IC1.28 (D2), IC3.12 (D2), R9.2, RP1.5
D3: IC1.26 (D3), IC3.8 (D3), R8.2, RP1.8
D4: IC1.24 (D4), IC3.7 (D4), R7.2, RP1.9
D5: IC1.23 (D5), IC3.9 (D5), R11.2, RP1.7
D6: IC1.21 (D6), IC3.10 (D6), R12.2, RP1.6
D7: IC1.19 (D7), IC3.13 (D7), R13.2, RP1.4
D'0: IC2.9 (D0), IC4.11 (D0), IC4B.14 (D0), K1.A4 (4A), R14.1
D'1: IC2.10 (D1), IC4.12 (D1), IC4B.13 (D1), K1.A5 (5A), R10.1
D'2: IC2.11 (D2), IC4.16 (D4), IC4A.11 (D3), K1.A6 (6A), R9.1
D'3: IC2.13 (D3), IC4.18 (D6), IC4A.13 (D1), K1.A9 (9A), R8.1
D'4: IC2.14 (D4), IC4.19 (D7), IC4A.14 (D0), K1.A10 (10A), R7.1
D'5: IC2.15 (D5), IC4.13 (D2), IC4B.12 (D2), K1.A8 (8A), R11.1
D'6: IC2.16 (D6), IC4.15 (D3), IC4B.11 (D3), K1.A7 (7A), R12.1
D'7: IC2.17 (D7), IC4.17 (D5), IC4A.12 (D2), K1.A1 (1A), R13.1
GND: C2.2, C3.-, C4.2, C5.-, C8.2, C9.2, C11.2, IC1.34 (GND), IC2.12 (GND), IC3.29 (GND), IC4.14 (GND), IC4A.9 (GND), IC4B.9 (GND), K1.B4 (4B), K1.B5 (5B), K2.2, K3.2, K4.2, R3.1, R27.1, R30.2, R31.1, R34.1, REG1.GND, T2.3 (E), X1.1, _R4.1
KBD0: IC1.33 (KBD0), KB1.P$1 (1), RP3.2
KBD1: IC1.31 (KBD1), KB1.P$2 (2), RP3.3
KBD2: IC1.29 (KBD2), KB1.P$3 (3), RP3.4
KBD3: IC1.27 (KBD3), KB1.P$4 (4), RP3.5
KBD4: IC1.25 (KBD4), KB1.P$5 (5), RP3.6
unnamed: IC1.12 (RAMCS), R2.1
unnamed: IC1.13 (ROMCS), R28.1
unnamed: C1.2, R1.2, T1.1 (B)
unnamed: C6.2, X1.2
unnamed: C6.1, IC1.35 (OSC), _R4.2
unnamed: C7.2, R3.2, R6.2, T2.1 (B)
unnamed: C3.+, K4.1, K4.1', REG1.IN
unnamed: D1.A, KB2.P$1 (1)
unnamed: D2.A, KB2.P$2 (2)
unnamed: D3.A, KB2.P$3 (3)
unnamed: D4.A, KB2.P$4 (4)
unnamed: D5.A, KB2.P$5 (5)
unnamed: D6.A, KB2.P$6 (6)
unnamed: D7.A, KB2.P$7 (7)
unnamed: D8.A, KB2.P$8 (8)
unnamed: C10.2, R33.1
unnamed: C12.2, R29.1
unnamed: D9.C, R32.2
unnamed: R31.2, R32.1
PHI: C7.1, IC1.14 (CLK), K1.B6 (6B), R6.1
TAPEIN: IC1.20 (TAPE_IN), R33.2
TAPE_IN: C10.1, K3.1, K3.1', R34.2
TAPE_OUT: C11.1, C12.1, K2.1, K2.1', R27.2
USA/UK: IC1.22 (USA/UK), R30.1
VIDEO: D9.A, IC1.16 (TV/TAPE), R29.2
